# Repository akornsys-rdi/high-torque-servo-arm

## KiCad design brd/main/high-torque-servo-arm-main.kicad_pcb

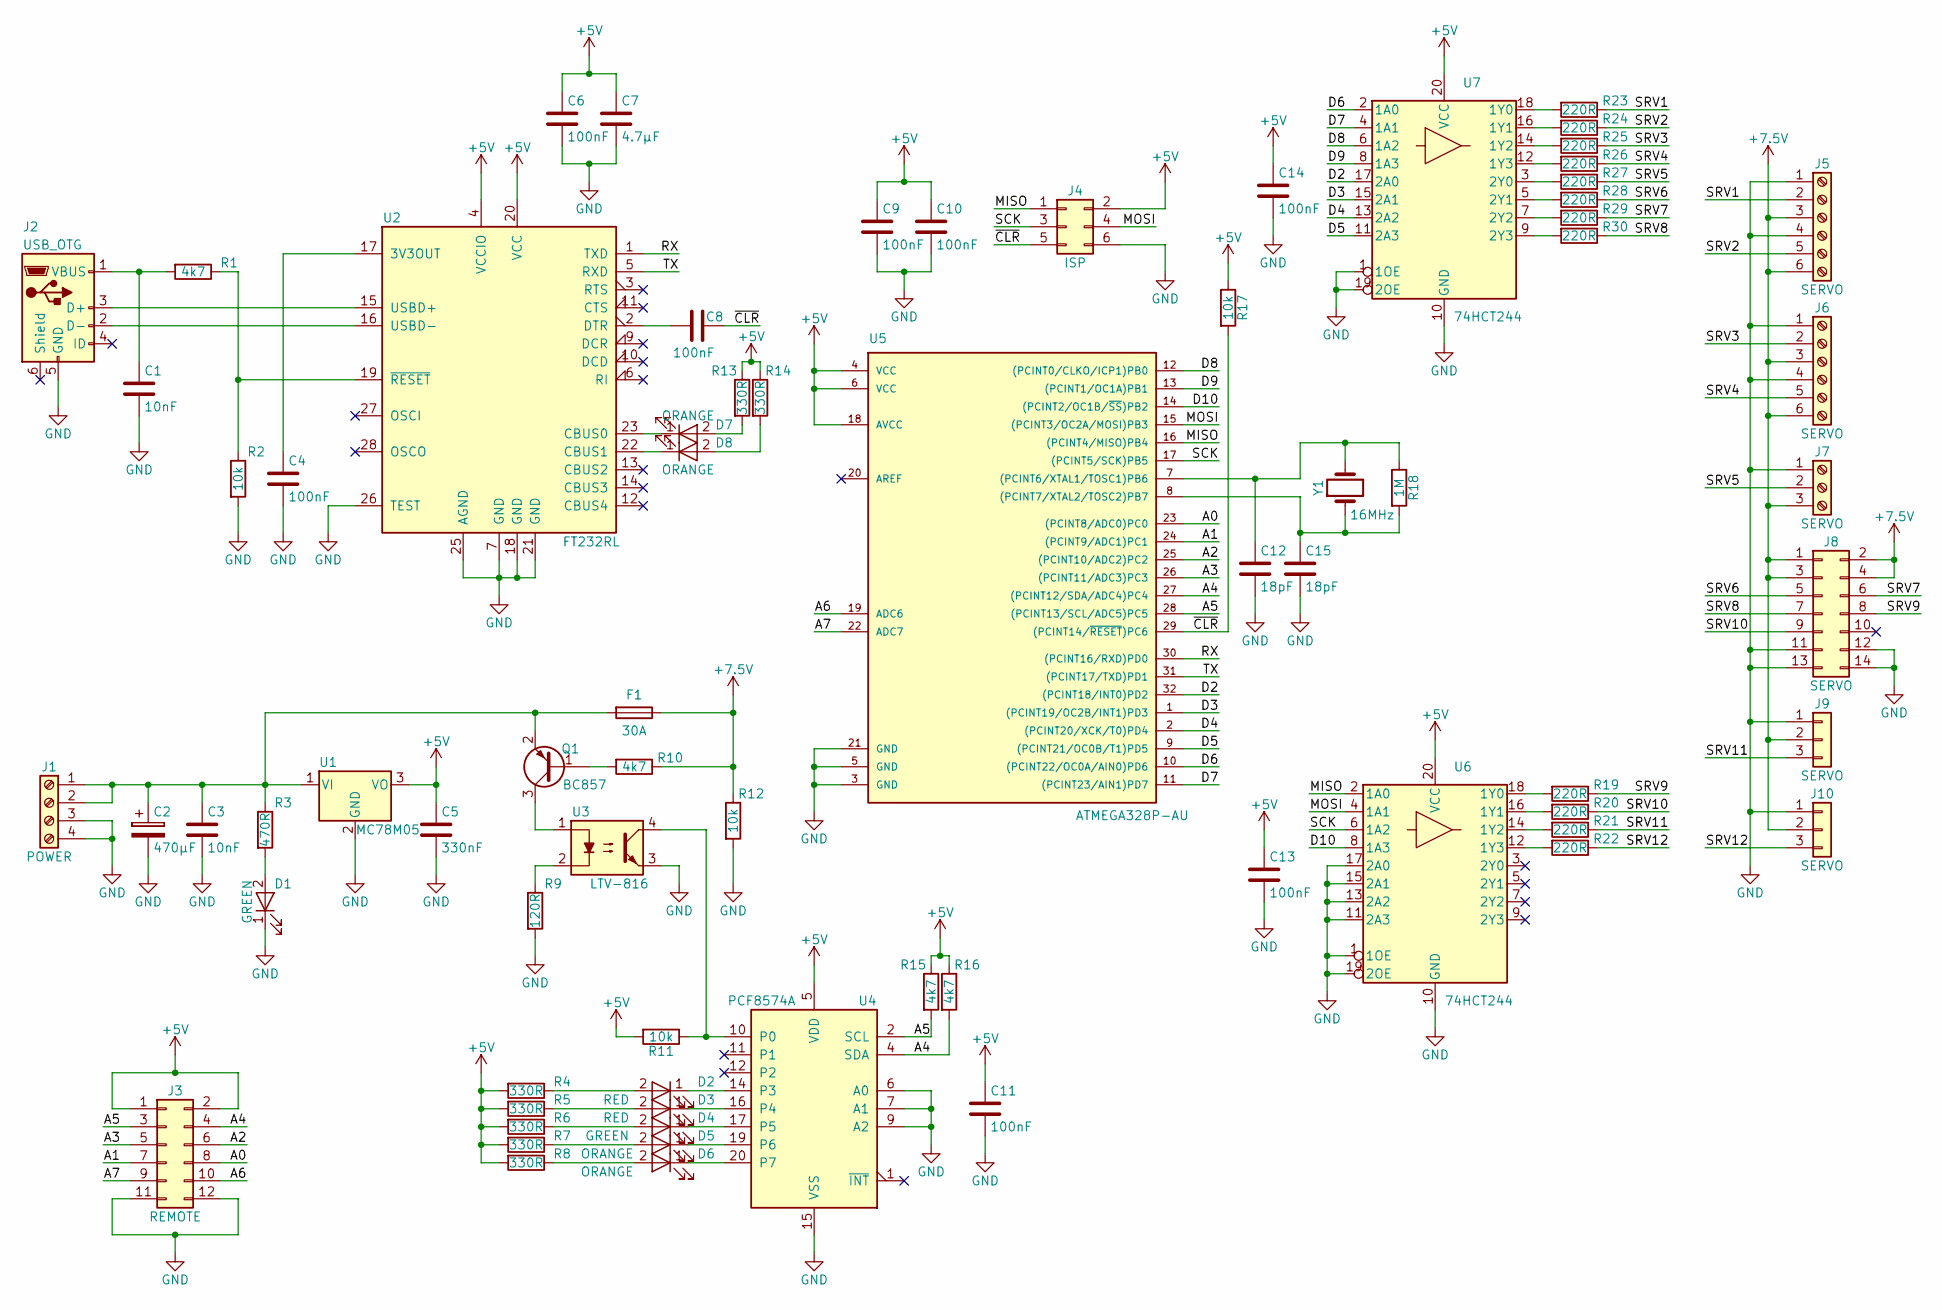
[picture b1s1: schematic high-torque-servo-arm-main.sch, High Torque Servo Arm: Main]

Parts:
C1, C3: 10nF; C_0805; Manufacturer Part Number C0805C103K1RACTU
C2: 470µF; CP_Elec_10x10.5; Manufacturer Part Number EEE-FC1A471P
C4, C6, C8, C9, C10, C11, C13, C14: 100nF; C_0805; Manufacturer Part Number C0805C104J5RACTU
C5: 330nF; C_0805; Manufacturer Part Number C0805C334K4RACTU
C7: 4.7µF; C_0805; Manufacturer Part Number C0805C475K8PACTU
C12, C15: 18pF; C_0805; Manufacturer Part Number C0805C180J5GAC
D1, D4: GREEN; LED_0805; Manufacturer Part Number LG R971-KN-1
D2, D3: RED; LED_0805; Manufacturer Part Number AP2012SRCPRV
D5, D6, D7, D8: ORANGE; LED_0805; Manufacturer Part Number LO R976-PS-1
F1: 30A; 3557; Manufacturer Part Number 3557-15
J1: POWER; 4DB-P108-04; Manufacturer Part Number 4DB-P108-04
J2: USB_OTG; USB_Mini-B; Manufacturer Part Number UJ2-MBH-1-SMT-TR
J3: REMOTE; IDC-Header_2x06_Pitch2.54mm_Straight; Manufacturer Part Number 70246-1201
J4: ISP; IDC-Header_2x03_Pitch2.54mm_Straight; Manufacturer Part Number 61200621621
J5, J6: SERVO; 1762075; Manufacturer Part Number 1762075
J7: SERVO; 1759020; Manufacturer Part Number 1759020
J8: SERVO; 61201422021; Manufacturer Part Number 61201422021
J9, J10: SERVO; Pin_Header_Straight_1x03_Pitch2.54mm; Manufacturer Part Number 22-28-9034
Q1: BC857; SOT-23; Manufacturer Part Number BC857CLT1G
R1, R10, R15, R16: 4k7; R_0805_HandSoldering; Manufacturer Part Number CR0805-JW-472ELF
R2, R11, R12, R17: 10k; R_0805_HandSoldering; Manufacturer Part Number CR0805-JW-103ELF
R3: 470R; R_0805_HandSoldering; Manufacturer Part Number CR0805-JW-471ELF
R4, R5, R6, R7, R8, R13, R14: 330R; R_0805_HandSoldering; Manufacturer Part Number CR0805-JW-331ELF
R9: 120R; R_0805_HandSoldering; Manufacturer Part Number CR0805-JW-121ELF
R18: 1M; R_0805_HandSoldering; Manufacturer Part Number CR0805-JW-105ELF
R19, R20, R21, R22, R23, R24, R25, R26, R27, R28, R29, R30: 220R; R_0805_HandSoldering; Manufacturer Part Number CR0805-JW-221ELF
U1: MC78M05; TO-252-2; Manufacturer Part Number MC78M05CDTRKG
U2: FT232RL; SSOP-28_5.3x10.2mm_Pitch0.65mm; Manufacturer Part Number FT232RL-REEL
U3: LTV-816; DIP-4_W8.89mm_SMDSocket_LongPads; Manufacturer Part Number LTV-816S
U4: PCF8574A; TSSOP-20_4.4x6.5mm_Pitch0.65mm; Manufacturer Part Number PCF8574APWRE4
U5: ATMEGA328P-AU; TQFP-32_7x7mm_Pitch0.8mm; Manufacturer Part Number ATMEGA328P-AU
U6, U7: 74HCT244; SSOP-20_5.3x7.2mm_Pitch0.65mm; Manufacturer Part Number SN74LV244ADBR
Y1: 16MHz; Crystal_SMD_HC49-SD; Manufacturer Part Number ABLS-16.000MHZ-B4-T

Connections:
+5V: C5.1, C6.1, C7.1, C9.1, C10.1, C11.1, C13.1, C14.1, J3.1, J3.2, J4.2, R4.2, R5.2, R6.2, R7.2, R8.2, R11.2, R13.1, R14.1, R15.1, R16.1, R17.1, U1.3 (VO), U2.4 (VCCIO), U2.20 (VCC), U4.5 (VDD), U5.4 (VCC), U5.6 (VCC), U5.18 (AVCC), U6.20 (VCC), U7.20 (VCC)
+7.5V: F1.1, J5.3, J5.6, J6.3, J6.6, J7.3, J8.1, J8.2, J8.3, J8.4, J9.2, J10.2, R10.1, R12.1
/A0: J3.8, U5.23 ((PCINT8/ADC0)PC0)
/A1: J3.7, U5.24 ((PCINT9/ADC1)PC1)
/A2: J3.6, U5.25 ((PCINT10/ADC2)PC2)
/A3: J3.5, U5.26 ((PCINT11/ADC3)PC3)
/A4: J3.4, R16.2, U4.4 (SDA), U5.27 ((PCINT12/SDA/ADC4)PC4)
/A5: J3.3, R15.2, U4.2 (SCL), U5.28 ((PCINT13/SCL/ADC5)PC5)
/A6: J3.10, U5.19 (ADC6)
/A7: J3.9, U5.22 (ADC7)
/D2: U5.32 ((PCINT18/INT0)PD2), U7.17 (2A0)
/D3: U5.1 ((PCINT19/OC2B/INT1)PD3), U7.15 (2A1)
/D4: U5.2 ((PCINT20/XCK/T0)PD4), U7.13 (2A2)
/D5: U5.9 ((PCINT21/OC0B/T1)PD5), U7.11 (2A3)
/D6: U5.10 ((PCINT22/OC0A/AIN0)PD6), U7.2 (1A0)
/D7: U5.11 ((PCINT23/AIN1)PD7), U7.4 (1A1)
/D8: U5.12 ((PCINT0/CLKO/ICP1)PB0), U7.6 (1A2)
/D9: U5.13 ((PCINT1/OC1A)PB1), U7.8 (1A3)
/D10: U5.14 ((PCINT2/OC1B/~SS~)PB2), U6.8 (1A3)
/MISO: J4.1, U5.16 ((PCINT4/MISO)PB4), U6.2 (1A0)
/MOSI: J4.4, U5.15 ((PCINT3/OC2A/MOSI)PB3), U6.4 (1A1)
/RX: U2.1 (TXD), U5.30 ((PCINT16/RXD)PD0)
/SCK: J4.3, U5.17 ((PCINT5/SCK)PB5), U6.6 (1A2)
/SRV1: J5.2, R23.1
/SRV2: J5.5, R24.1
/SRV3: J6.2, R25.1
/SRV4: J6.5, R26.1
/SRV5: J7.2, R27.1
/SRV6: J8.5, R28.1
/SRV7: J8.6, R29.1
/SRV8: J8.7, R30.1
/SRV9: J8.8, R19.1
/SRV10: J8.9, R20.1
/SRV11: J9.3, R21.1
/SRV12: J10.3, R22.1
/TX: U2.5 (RXD), U5.31 ((PCINT17/TXD)PD1)
/~CLR: C8.2, J4.5, R17.2, U5.29 ((PCINT14/~RESET~)PC6)
GND: C1.2, C2.2, C3.2, C4.2, C5.2, C6.2, C7.2, C9.2, C10.2, C11.2, C12.2, C13.2, C14.2, C15.2, D1.1 (K), J1.3, J1.4, J2.5 (GND), J3.11, J3.12, J4.6, J5.1, J5.4, J6.1, J6.4, J7.1, J8.11, J8.12, J8.13, J8.14, J9.1, J10.1, R2.2, R9.2, R12.2, U1.2 (GND), U2.7 (GND), U2.18 (GND), U2.21 (GND), U2.25 (AGND), U2.26 (TEST), U3.3, U4.6 (A0), U4.7 (A1), U4.9 (A2), U4.15 (VSS), U5.3 (GND), U5.5 (GND), U5.21 (GND), U6.1 (1OE), U6.10 (GND), U6.11 (2A3), U6.13 (2A2), U6.15 (2A1), U6.17 (2A0), U6.19 (2OE), U7.1 (1OE), U7.10 (GND), U7.19 (2OE)
unnamed: C1.1, J2.1 (VBUS), R1.2
unnamed: C2.1, C3.1, F1.2, J1.1, J1.2, Q1.2 (E), R3.1, U1.1 (VI)
unnamed: C4.1, U2.17 (3V3OUT)
unnamed: C8.1, U2.2 (DTR)
unnamed: C12.1, R18.1, U5.7 ((PCINT6/XTAL1/TOSC1)PB6), Y1.2
unnamed: C15.1, R18.2, U5.8 ((PCINT7/XTAL2/TOSC2)PB7), Y1.1
unnamed: D1.2 (A), R3.2
unnamed: D2.1 (K), U4.14 (P3)
unnamed: D2.2 (A), R4.1
unnamed: D3.1 (K), U4.16 (P4)
unnamed: D3.2 (A), R5.1
unnamed: D4.1 (K), U4.17 (P5)
unnamed: D4.2 (A), R6.1
unnamed: D5.1 (K), U4.19 (P6)
unnamed: D5.2 (A), R7.1
unnamed: D6.1 (K), U4.20 (P7)
unnamed: D6.2 (A), R8.1
unnamed: D7.1 (K), U2.23 (CBUS0)
unnamed: D7.2 (A), R13.2
unnamed: D8.1 (K), U2.22 (CBUS1)
unnamed: D8.2 (A), R14.2
unnamed: J2.2 (D-), U2.16 (USBD-)
unnamed: J2.3 (D+), U2.15 (USBD+)
unnamed: Q1.1 (B), R10.2
unnamed: Q1.3 (C), U3.1
unnamed: R1.1, R2.1, U2.19 (~RESET~)
unnamed: R9.1, U3.2
unnamed: R11.1, U3.4, U4.10 (P0)
unnamed: R19.2, U6.18 (1Y0)
unnamed: R20.2, U6.16 (1Y1)
unnamed: R21.2, U6.14 (1Y2)
unnamed: R22.2, U6.12 (1Y3)
unnamed: R23.2, U7.18 (1Y0)
unnamed: R24.2, U7.16 (1Y1)
unnamed: R25.2, U7.14 (1Y2)
unnamed: R26.2, U7.12 (1Y3)
unnamed: R27.2, U7.3 (2Y0)
unnamed: R28.2, U7.5 (2Y1)
unnamed: R29.2, U7.7 (2Y2)
unnamed: R30.2, U7.9 (2Y3)
unnamed: U4.3 (NC), U4.8 (NC), U4.13 (NC), U4.18 (NC)

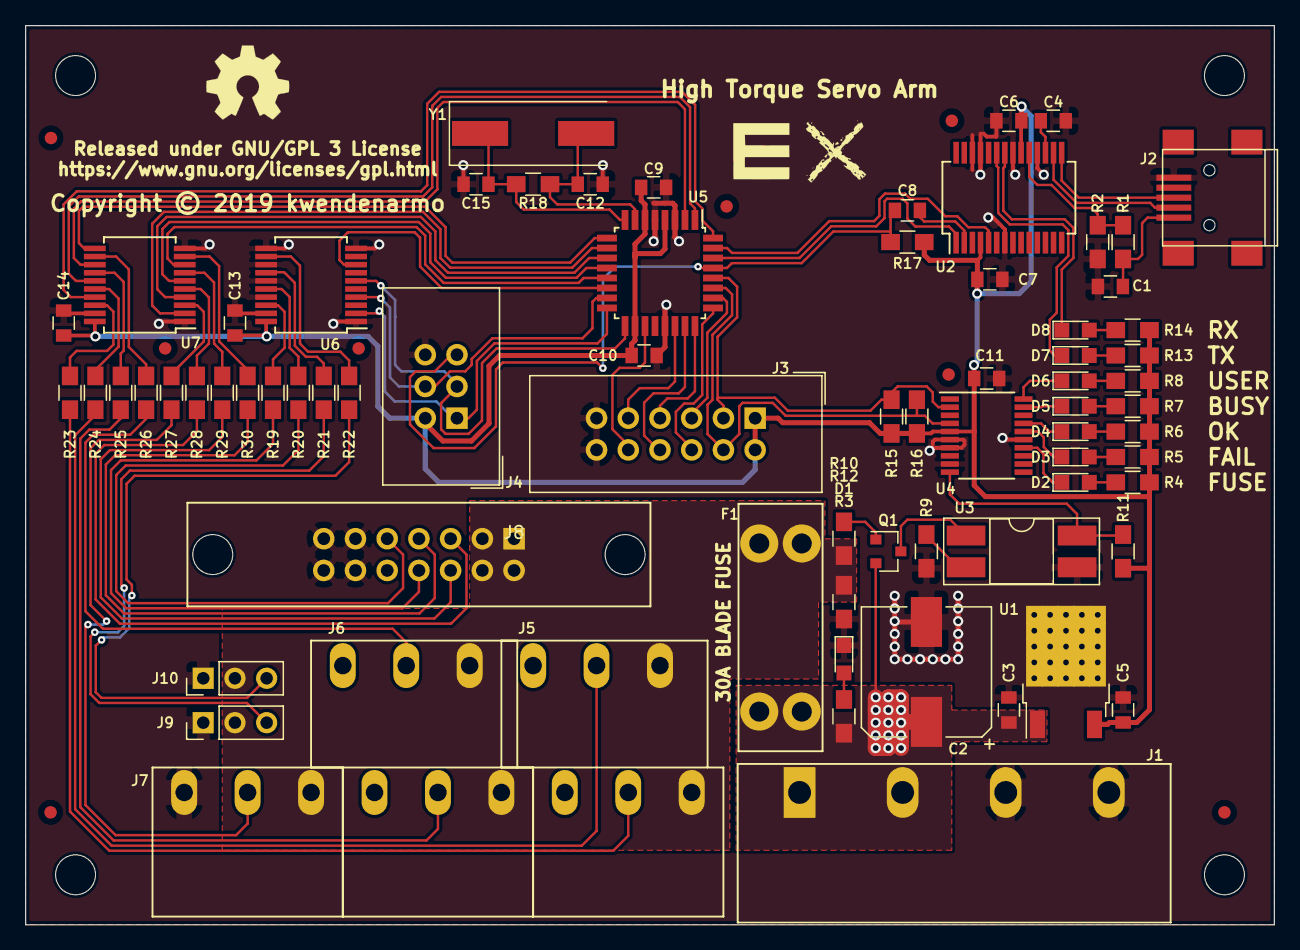
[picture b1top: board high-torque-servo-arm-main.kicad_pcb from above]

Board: 2 copper layers, 100.0 x 72.0 mm, 73 parts (0 on the bottom side), 79 nets.

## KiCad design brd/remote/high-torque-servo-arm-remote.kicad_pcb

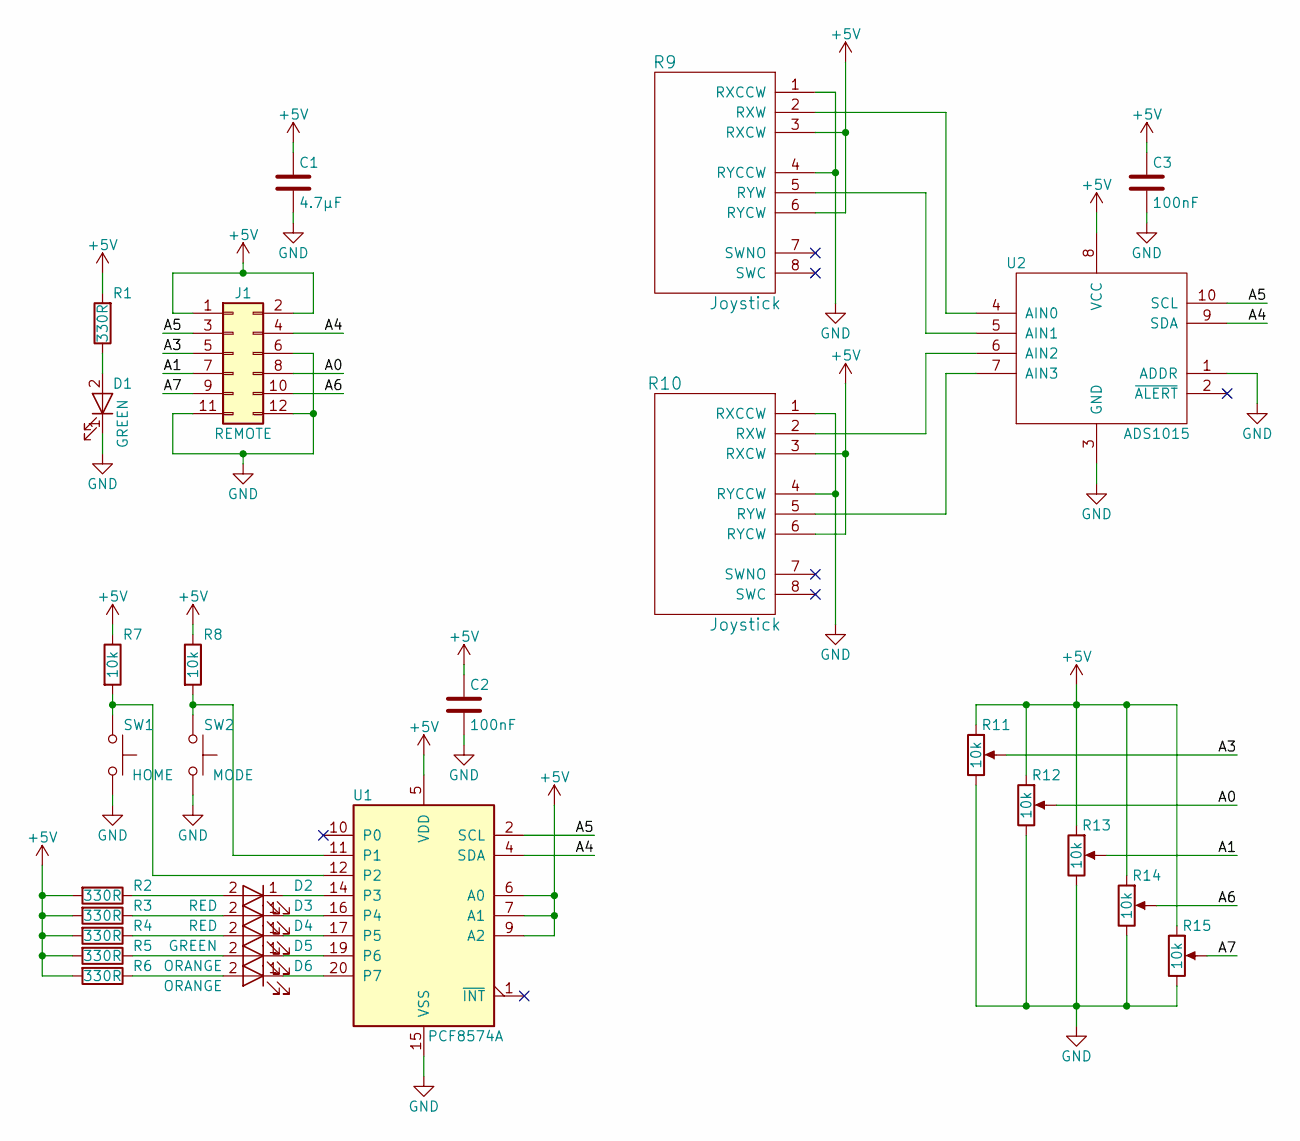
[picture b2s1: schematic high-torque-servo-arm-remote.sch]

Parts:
C1: 4.7µF; C_0805; Manufacturer Part Number C0805C475K8PACTU
C2, C3: 100nF; C_0805; Manufacturer Part Number C0805C104J5RACTU
D1, D4: GREEN; LED_0805_HandSoldering; Manufacturer Part Number LG R971-KN-1
D2, D3: RED; LED_0805_HandSoldering; Manufacturer Part Number AP2012SRCPRV
D5, D6: ORANGE; LED_0805_HandSoldering; Manufacturer Part Number LO R976-PS-1
J1: REMOTE; IDC-Header_2x06_Pitch2.54mm_Straight; Manufacturer Part Number 70246-1201
R1, R2, R3, R4, R5, R6: 330R; R_0805_HandSoldering; Manufacturer Part Number CR0805-JW-331ELF
R7, R8: 10k; R_0805_HandSoldering; Manufacturer Part Number CR0805-JW-103ELF
R9, R10: Joystick; 311110005; Manufacturer Part Number 311110005
R11, R12, R13, R14, R15: 10k; RS08U111Z001; Manufacturer Part Number RS08U111Z001
SW1: HOME; SW_PUSH_6mm_h4.3mm; Manufacturer Part Number FSM4JH
SW2: MODE; SW_PUSH_6mm_h4.3mm; Manufacturer Part Number FSM4JH
U1: PCF8574A; TSSOP-20_4.4x6.5mm_Pitch0.65mm; Manufacturer Part Number PCF8574APWRE4
U2: ADS1015; MSOP-10_3x3mm_Pitch0.5mm; Manufacturer Part Number ADS1015IDGSR

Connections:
+5V: C1.1, C2.1, C3.1, J1.1, J1.2, R1.2, R2.2, R3.2, R4.2, R5.2, R6.2, R7.1, R8.1, R9.3 (RXCW), R9.6 (RYCW), R10.3 (RXCW), R10.6 (RYCW), R11.1, R12.1, R13.1, R14.1, R15.1, U1.5 (VDD), U1.6 (A0), U1.7 (A1), U1.9 (A2), U2.8 (VCC)
/A0: J1.8, R12.2
/A1: J1.7, R13.2
/A3: J1.5, R11.2
/A4: J1.4, U1.4 (SDA), U2.9 (SDA)
/A5: J1.3, U1.2 (SCL), U2.10 (SCL)
/A6: J1.10, R14.2
/A7: J1.9, R15.2
GND: C1.2, C2.2, C3.2, D1.1 (K), J1.6, J1.11, J1.12, R9.1 (RXCCW), R9.4 (RYCCW), R10.1 (RXCCW), R10.4 (RYCCW), R11.3, R12.3, R13.3, R14.3, R15.3, SW1.2, SW2.2, U1.15 (VSS), U2.1 (ADDR), U2.3 (GND)
unnamed: D1.2 (A), R1.1
unnamed: D2.1 (K), U1.14 (P3)
unnamed: D2.2 (A), R2.1
unnamed: D3.1 (K), U1.16 (P4)
unnamed: D3.2 (A), R3.1
unnamed: D4.1 (K), U1.17 (P5)
unnamed: D4.2 (A), R4.1
unnamed: D5.1 (K), U1.19 (P6)
unnamed: D5.2 (A), R5.1
unnamed: D6.1 (K), U1.20 (P7)
unnamed: D6.2 (A), R6.1
unnamed: R7.2, SW1.1, U1.12 (P2)
unnamed: R8.2, SW2.1, U1.11 (P1)
unnamed: R9.2 (RXW), U2.4 (AIN0)
unnamed: R9.5 (RYW), U2.5 (AIN1)
unnamed: R10.2 (RXW), U2.6 (AIN2)
unnamed: R10.5 (RYW), U2.7 (AIN3)
unnamed: U1.3 (NC), U1.8 (NC), U1.13 (NC), U1.18 (NC)

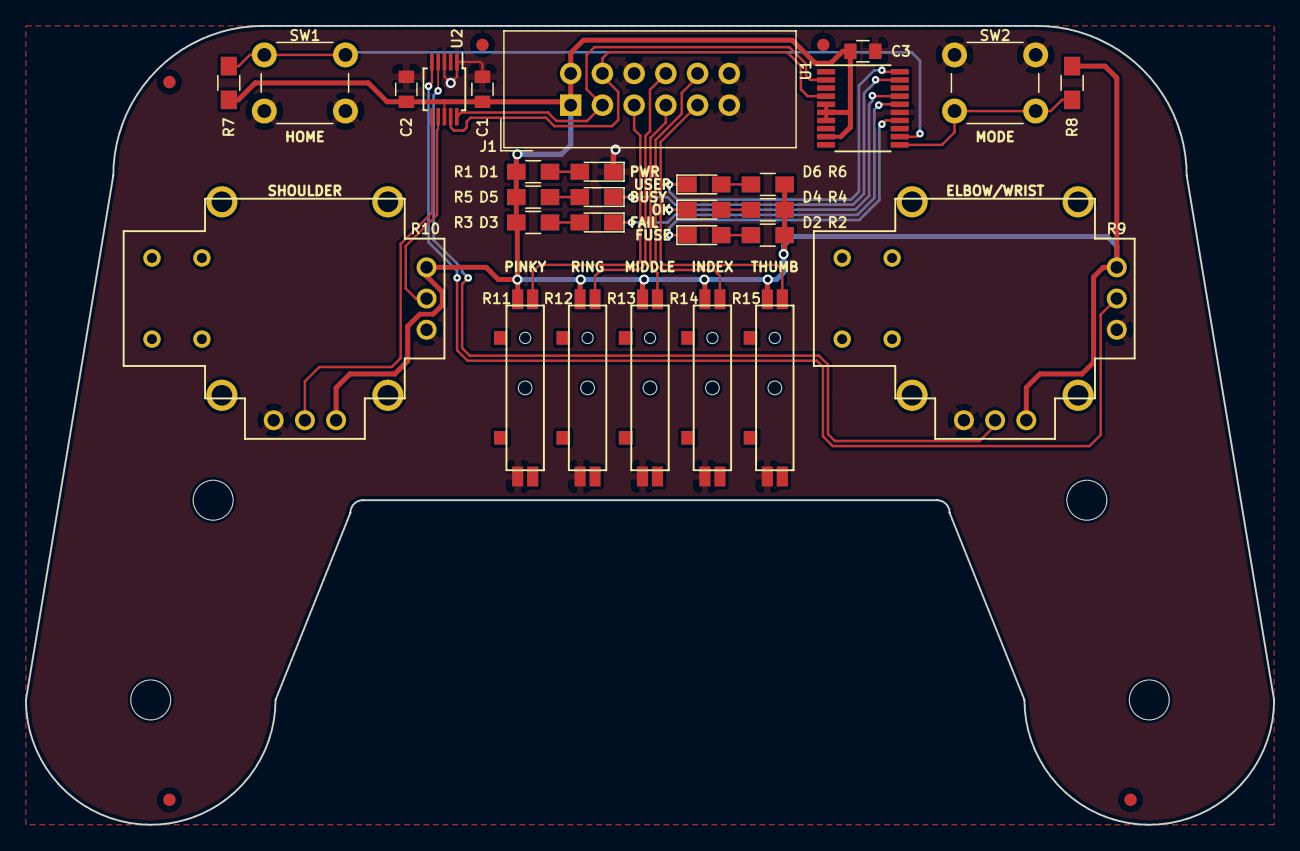
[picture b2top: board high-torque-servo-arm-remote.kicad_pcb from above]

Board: 2 copper layers, 100.0 x 64.0 mm, 29 parts (0 on the bottom side), 27 nets.

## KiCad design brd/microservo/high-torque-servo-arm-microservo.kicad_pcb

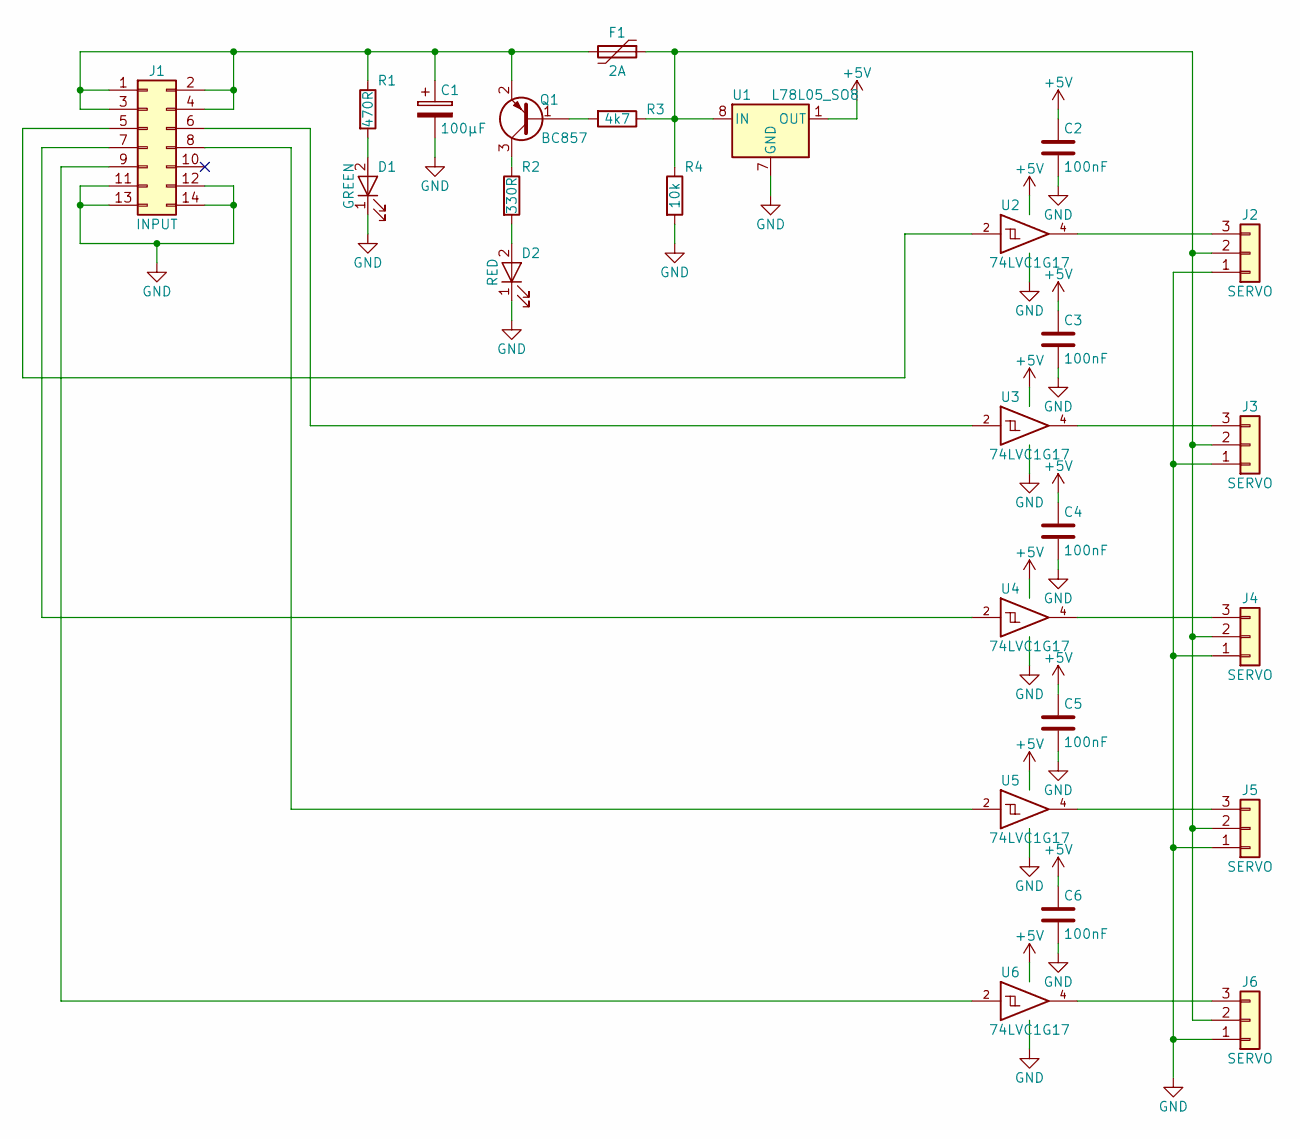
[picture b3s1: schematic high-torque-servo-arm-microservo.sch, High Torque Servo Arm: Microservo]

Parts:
C1: 100µF; CP_Elec_6.3x7.7; Manufacturer Part Number EEE-HC1C101XP
C2, C3, C4, C5, C6: 100nF; C_0805; Manufacturer Part Number C0805C104J5RACTU
D1: GREEN; LED_0805; Manufacturer Part Number LG R971-KN-1
D2: RED; LED_0805; Manufacturer Part Number AP2012SRCPRV
F1: 2A; Fuse_SMD2920; Manufacturer Part Number 0ZCF0200FF2C
J1: INPUT; 61201422021; Manufacturer Part Number 61201422021
J2, J3, J4, J5, J6: SERVO; Pin_Header_Angled_1x03_Pitch2.54mm; Manufacturer Part Number 22-28-9034
Q1: BC857; SOT-23; Manufacturer Part Number BC857CLT1G
R1: 470R; R_0805_HandSoldering; Manufacturer Part Number CR0805-JW-471ELF
R2: 330R; R_0805_HandSoldering; Manufacturer Part Number CR0805-JW-331ELF
R3: 4k7; R_0805_HandSoldering; Manufacturer Part Number CR0805-JW-472ELF
R4: 10k; R_0805_HandSoldering; Manufacturer Part Number CR0805-JW-103ELF
U1: L78L05_SO8; SOIC-8_3.9x4.9mm_Pitch1.27mm; Manufacturer Part Number L78L05ABD13TR
U2, U3, U4, U5, U6: 74LVC1G17; SOT-23-5; Manufacturer Part Number SN74LVC1G17DBVR

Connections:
+5V: C2.1, C3.1, C4.1, C5.1, C6.1, U1.1 (OUT), U2.5 (VCC), U3.5 (VCC), U4.5 (VCC), U5.5 (VCC), U6.5 (VCC)
GND: C1.2, C2.2, C3.2, C4.2, C5.2, C6.2, D1.1 (K), D2.1 (K), J1.11, J1.12, J1.13, J1.14, J2.1, J3.1, J4.1, J5.1, J6.1, R4.2, U1.2 (GND), U1.3 (GND), U1.6 (GND), U1.7 (GND), U2.3 (GND), U3.3 (GND), U4.3 (GND), U5.3 (GND), U6.3 (GND)
unnamed: C1.1, F1.2, J1.1, J1.2, J1.3, J1.4, Q1.2 (E), R1.1
unnamed: D1.2 (A), R1.2
unnamed: D2.2 (A), R2.2
unnamed: F1.1, J2.2, J3.2, J4.2, J5.2, J6.2, R3.1, R4.1, U1.8 (IN)
unnamed: J1.5, U2.2
unnamed: J1.6, U3.2
unnamed: J1.7, U4.2
unnamed: J1.8, U5.2
unnamed: J1.9, U6.2
unnamed: J2.3, U2.4
unnamed: J3.3, U3.4
unnamed: J4.3, U4.4
unnamed: J5.3, U5.4
unnamed: J6.3, U6.4
unnamed: Q1.1 (B), R3.2
unnamed: Q1.3 (C), R2.1

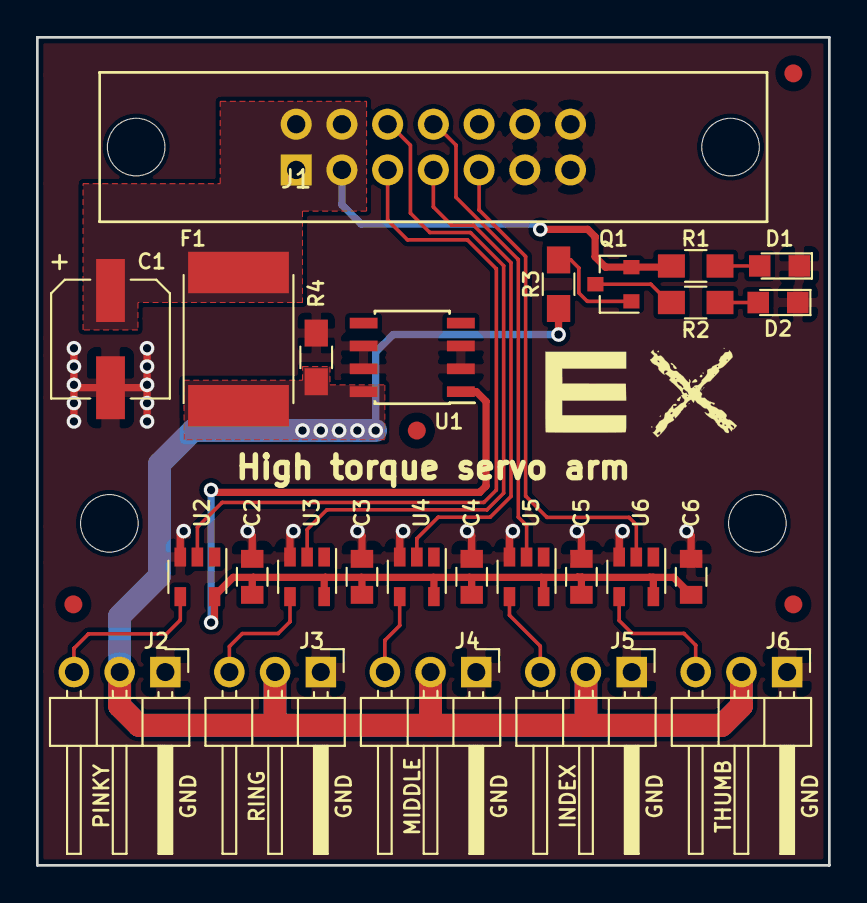
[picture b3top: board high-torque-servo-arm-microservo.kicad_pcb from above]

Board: 2 copper layers, 44.0 x 46.0 mm, 26 parts (0 on the bottom side), 18 nets.

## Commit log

2019-12-06 añadido diseño de pcb servo
2019-12-06 añadido diseño de pcb microservo
2019-12-08 corregido tamaño de taladro en huella
2019-12-08 añadido diseño de pcb main
2020-02-25 actualizado diseño de pcb y añadida remote
2020-02-25 subido códigos de autotest
2020-02-25 subidos archivos 3d
2020-02-26 añadido código de control principal
2023-08-11 subidos archivos !WIP

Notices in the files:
brd/main/high-torque-servo-arm-main.kicad_pcb:
Released under GNU/GPL 3 License
https://www.gnu.org/licenses/gpl.html
Copyright © 2019 kwendenarmo
